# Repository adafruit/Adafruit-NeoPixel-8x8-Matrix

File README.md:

# Adafruit-NeoPixel-8x8-Matrix 

__Format is EagleCAD schematic and board layout__

<a href="http://www.adafruit.com/products/1487"><br/>Click here to purchase one from the Adafruit shop</a>

Put on your sunglasses before wiring up this LED matrix - 64 eye-blistering RGB LEDs adorn the NeoMatrix for a blast of configurable color. Arranged in an 8x8 matrix, each pixel is individually addressable. Only one microcontroller pin is required to control all the LEDs, and you get 24 bit color for each LED.

Wiring it up is easy: there are two 3-pin connection ports. Solder wires to the input port and provide 5VDC to the +5V and ground pins, then connect the DIN pin to your microcontroller. If you're using our NeoPixel Arduino library, use digital #6. You'll also need to make a common ground from the 5V power supply to the microcontroller/Arduino. Since each LED can draw as much as 60mA (thats up to 3.5 Amps per panel if all LEDs are on bright white!) we suggest our 5V 2A power supply. For most uses, you'll see about 1-2A of current per panel.

If, say, you need MORE blinky, you can chain these together. For the second shield, connect the DIN connection to the first panel's DOUT. Also connect a ground pin together and power with 5V. There you go! You can chain as many as you'd like although after 4 or more panels you may run low on RAM if you're using an UNO. Watch your power usage too, you may need a 5V 10A power supply for so many of these!

There is a single data line with a very timing-specific protocol. Since the protocol is very sensitive to timing, it requires a real-time microconroller such as an AVR, Arduino, PIC, mbed, etc. It cannot be used with a Linux-based microcomputer or interpreted microcontroller such as the netduino or Basic Stamp. Our wonderfully-written Neopixel library for Arduino supports these pixels! As it requires hand-tuned assembly it is only for AVR cores but others may have ported this chip driver code so please google around. An 8MHz or faster processor is required.

[Our detailed NeoPixel Uberguide has everything you need to use NeoPixels in any shape and size. Including ready-to-go library & example code for the Arduino UNO/Duemilanove/Diecimila, Flora/Micro/Leonardo, Trinket/Gemma, Arduino Due & Arduino Mega/ADK (all versions)](http://learn.adafruit.com/adafruit-neopixel-uberguide)

## License

Adafruit invests time and resources providing this open source design, 
please support Adafruit and open-source hardware by purchasing 
products from Adafruit!

Designed by Adafruit Industries.  
Creative Commons Attribution, Share-Alike license, check license.txt for more information
All text above must be included in any redistribution

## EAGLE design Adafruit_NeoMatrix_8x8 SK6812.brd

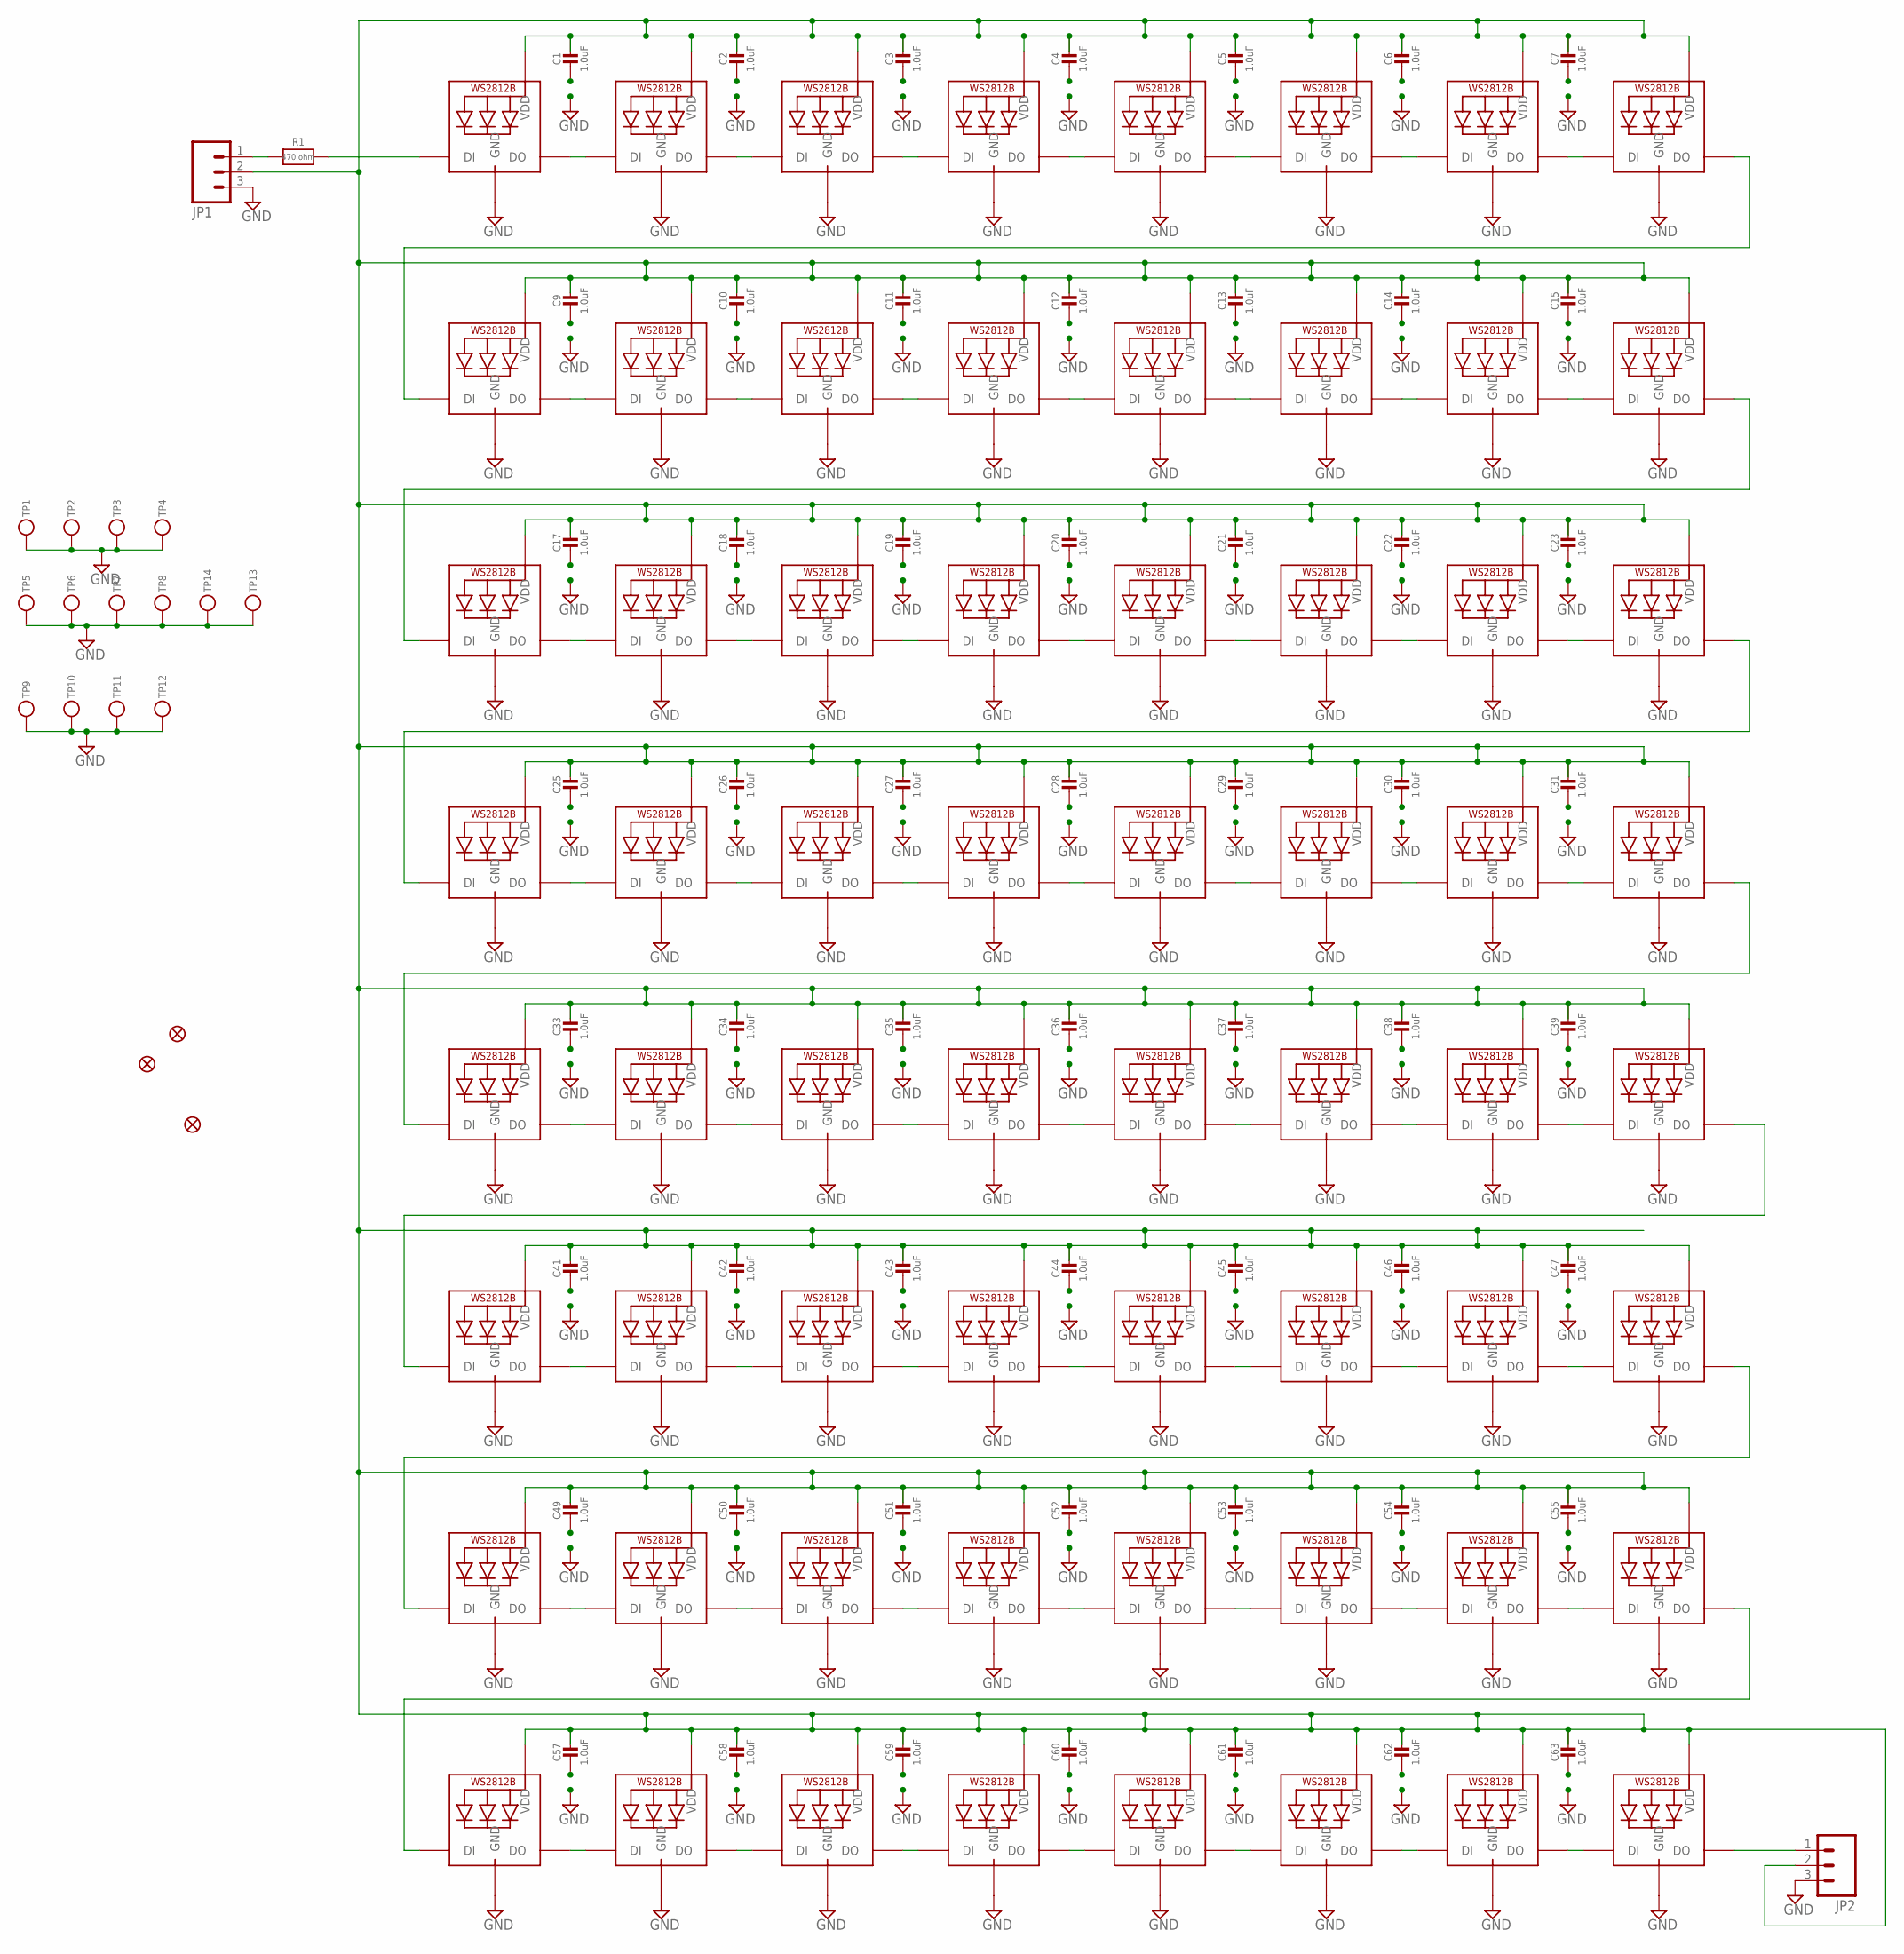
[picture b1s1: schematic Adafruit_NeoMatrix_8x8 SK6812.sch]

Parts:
C1, C2, C3, C4, C5, C6, C7, C9, C10, C11, C12, C13, C14, C15, C17, C18, C19, C20, C21, C22, C23, C25, C26, C27, C28, C29, C30, C31, C33, C34, C35, C36, C37, C38, C39, C41, C42, C43, C44, C45, C46, C47, C49, C50, C51, C52, C53, C54, C55, C57, C58, C59, C60, C61, C62, C63: 1.0uF; 0805-NO
FID1, FID2, FID3: FIDUCIAL_1MM
JP1, JP2: M03PTH; 1X03
LED1, LED2, LED3, LED4, LED5, LED6, LED7, LED8, LED9, LED10, LED11, LED12, LED13, LED14, LED15, LED16, LED17, LED18, LED19, LED20, LED21, LED22, LED23, LED24, LED25, LED26, LED27, LED28, LED29, LED30, LED31, LED32, LED33, LED34, LED35, LED36, LED37, LED38, LED39, LED40, LED41, LED42, LED43, LED44, LED45, LED46, LED47, LED48, LED49, LED50, LED51, LED52, LED53, LED54, LED55, LED56, LED57, LED58, LED59, LED60, LED61, LED62, LED63, LED64: WS2812B5050; WS2812B
R1: 470 ohm; 0805-NO
TP1, TP2, TP3, TP4, TP5, TP6, TP7, TP8, TP9, TP10, TP11, TP12, TP13, TP14: TESTPOINT; TESTPOINT_SMT

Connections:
GND: C1.2, C2.2, C3.2, C4.2, C5.2, C6.2, C7.2, C9.2, C10.2, C11.2, C12.2, C13.2, C14.2, C15.2, C17.2, C18.2, C19.2, C20.2, C21.2, C22.2, C23.2, C25.2, C26.2, C27.2, C28.2, C29.2, C30.2, C31.2, C33.2, C34.2, C35.2, C36.2, C37.2, C38.2, C39.2, C41.2, C42.2, C43.2, C44.2, C45.2, C46.2, C47.2, C49.2, C50.2, C51.2, C52.2, C53.2, C54.2, C55.2, C57.2, C58.2, C59.2, C60.2, C61.2, C62.2, C63.2, JP1.3, JP2.3, LED1.3-GND (GND), LED2.3-GND (GND), LED3.3-GND (GND), LED4.3-GND (GND), LED5.3-GND (GND), LED6.3-GND (GND), LED7.3-GND (GND), LED8.3-GND (GND), LED9.3-GND (GND), LED10.3-GND (GND), LED11.3-GND (GND), LED12.3-GND (GND), LED13.3-GND (GND), LED14.3-GND (GND), LED15.3-GND (GND), LED16.3-GND (GND), LED17.3-GND (GND), LED18.3-GND (GND), LED19.3-GND (GND), LED20.3-GND (GND), LED21.3-GND (GND), LED22.3-GND (GND), LED23.3-GND (GND), LED24.3-GND (GND), LED25.3-GND (GND), LED26.3-GND (GND), LED27.3-GND (GND), LED28.3-GND (GND), LED29.3-GND (GND), LED30.3-GND (GND), LED31.3-GND (GND), LED32.3-GND (GND), LED33.3-GND (GND), LED34.3-GND (GND), LED35.3-GND (GND), LED36.3-GND (GND), LED37.3-GND (GND), LED38.3-GND (GND), LED39.3-GND (GND), LED40.3-GND (GND), LED41.3-GND (GND), LED42.3-GND (GND), LED43.3-GND (GND), LED44.3-GND (GND), LED45.3-GND (GND), LED46.3-GND (GND), LED47.3-GND (GND), LED48.3-GND (GND), LED49.3-GND (GND), LED50.3-GND (GND), LED51.3-GND (GND), LED52.3-GND (GND), LED53.3-GND (GND), LED54.3-GND (GND), LED55.3-GND (GND), LED56.3-GND (GND), LED57.3-GND (GND), LED58.3-GND (GND), LED59.3-GND (GND), LED60.3-GND (GND), LED61.3-GND (GND), LED62.3-GND (GND), LED63.3-GND (GND), LED64.3-GND (GND), TP1.P$1, TP2.P$1, TP3.P$1, TP4.P$1, TP5.P$1, TP6.P$1, TP7.P$1, TP8.P$1, TP9.P$1, TP10.P$1, TP11.P$1, TP12.P$1, TP13.P$1, TP14.P$1
unnamed: LED1.4-DIN (DI), R1.2
unnamed: LED8.2-DOUT (DO), LED9.4-DIN (DI)
unnamed: LED16.2-DOUT (DO), LED17.4-DIN (DI)
unnamed: LED24.2-DOUT (DO), LED25.4-DIN (DI)
unnamed: LED40.2-DOUT (DO), LED41.4-DIN (DI)
unnamed: LED32.2-DOUT (DO), LED33.4-DIN (DI)
unnamed: LED48.2-DOUT (DO), LED49.4-DIN (DI)
unnamed: LED56.2-DOUT (DO), LED57.4-DIN (DI)
unnamed: JP2.1, LED64.2-DOUT (DO)
unnamed: JP1.1, R1.1
unnamed: LED17.2-DOUT (DO), LED18.4-DIN (DI)
unnamed: LED25.2-DOUT (DO), LED26.4-DIN (DI)
unnamed: LED26.2-DOUT (DO), LED27.4-DIN (DI)
unnamed: LED2.2-DOUT (DO), LED3.4-DIN (DI)
unnamed: LED3.2-DOUT (DO), LED4.4-DIN (DI)
unnamed: LED4.2-DOUT (DO), LED5.4-DIN (DI)
unnamed: LED5.2-DOUT (DO), LED6.4-DIN (DI)
unnamed: LED6.2-DOUT (DO), LED7.4-DIN (DI)
unnamed: LED7.2-DOUT (DO), LED8.4-DIN (DI)
unnamed: LED10.2-DOUT (DO), LED11.4-DIN (DI)
unnamed: LED11.2-DOUT (DO), LED12.4-DIN (DI)
unnamed: LED12.2-DOUT (DO), LED13.4-DIN (DI)
unnamed: LED13.2-DOUT (DO), LED14.4-DIN (DI)
unnamed: LED14.2-DOUT (DO), LED15.4-DIN (DI)
unnamed: LED15.2-DOUT (DO), LED16.4-DIN (DI)
unnamed: LED18.2-DOUT (DO), LED19.4-DIN (DI)
unnamed: LED19.2-DOUT (DO), LED20.4-DIN (DI)
unnamed: LED20.2-DOUT (DO), LED21.4-DIN (DI)
unnamed: LED21.2-DOUT (DO), LED22.4-DIN (DI)
unnamed: LED22.2-DOUT (DO), LED23.4-DIN (DI)
unnamed: LED23.2-DOUT (DO), LED24.4-DIN (DI)
unnamed: LED27.2-DOUT (DO), LED28.4-DIN (DI)
unnamed: LED28.2-DOUT (DO), LED29.4-DIN (DI)
unnamed: LED29.2-DOUT (DO), LED30.4-DIN (DI)
unnamed: LED30.2-DOUT (DO), LED31.4-DIN (DI)
unnamed: LED31.2-DOUT (DO), LED32.4-DIN (DI)
unnamed: LED1.2-DOUT (DO), LED2.4-DIN (DI)
unnamed: LED9.2-DOUT (DO), LED10.4-DIN (DI)
unnamed: LED49.2-DOUT (DO), LED50.4-DIN (DI)
unnamed: LED57.2-DOUT (DO), LED58.4-DIN (DI)
unnamed: LED58.2-DOUT (DO), LED59.4-DIN (DI)
unnamed: LED34.2-DOUT (DO), LED35.4-DIN (DI)
unnamed: LED35.2-DOUT (DO), LED36.4-DIN (DI)
unnamed: LED36.2-DOUT (DO), LED37.4-DIN (DI)
unnamed: LED37.2-DOUT (DO), LED38.4-DIN (DI)
unnamed: LED38.2-DOUT (DO), LED39.4-DIN (DI)
unnamed: LED39.2-DOUT (DO), LED40.4-DIN (DI)
unnamed: LED42.2-DOUT (DO), LED43.4-DIN (DI)
unnamed: LED43.2-DOUT (DO), LED44.4-DIN (DI)
unnamed: LED44.2-DOUT (DO), LED45.4-DIN (DI)
unnamed: LED45.2-DOUT (DO), LED46.4-DIN (DI)
unnamed: LED46.2-DOUT (DO), LED47.4-DIN (DI)
unnamed: LED47.2-DOUT (DO), LED48.4-DIN (DI)
unnamed: LED50.2-DOUT (DO), LED51.4-DIN (DI)
unnamed: LED51.2-DOUT (DO), LED52.4-DIN (DI)
unnamed: LED52.2-DOUT (DO), LED53.4-DIN (DI)
unnamed: LED53.2-DOUT (DO), LED54.4-DIN (DI)
unnamed: LED54.2-DOUT (DO), LED55.4-DIN (DI)
unnamed: LED55.2-DOUT (DO), LED56.4-DIN (DI)
unnamed: LED59.2-DOUT (DO), LED60.4-DIN (DI)
unnamed: LED60.2-DOUT (DO), LED61.4-DIN (DI)
unnamed: LED61.2-DOUT (DO), LED62.4-DIN (DI)
unnamed: LED62.2-DOUT (DO), LED63.4-DIN (DI)
unnamed: LED63.2-DOUT (DO), LED64.4-DIN (DI)
unnamed: LED33.2-DOUT (DO), LED34.4-DIN (DI)
unnamed: LED41.2-DOUT (DO), LED42.4-DIN (DI)
VDD: C1.1, C2.1, C3.1, C4.1, C5.1, C6.1, C7.1, C9.1, C10.1, C11.1, C12.1, C13.1, C14.1, C15.1, C17.1, C18.1, C19.1, C20.1, C21.1, C22.1, C23.1, C25.1, C26.1, C27.1, C28.1, C29.1, C30.1, C31.1, C33.1, C34.1, C35.1, C36.1, C37.1, C38.1, C39.1, C41.1, C42.1, C43.1, C44.1, C45.1, C46.1, C47.1, C49.1, C50.1, C51.1, C52.1, C53.1, C54.1, C55.1, C57.1, C58.1, C59.1, C60.1, C61.1, C62.1, C63.1, JP1.2, JP2.2, LED1.1-VDD (VDD), LED2.1-VDD (VDD), LED3.1-VDD (VDD), LED4.1-VDD (VDD), LED5.1-VDD (VDD), LED6.1-VDD (VDD), LED7.1-VDD (VDD), LED8.1-VDD (VDD), LED9.1-VDD (VDD), LED10.1-VDD (VDD), LED11.1-VDD (VDD), LED12.1-VDD (VDD), LED13.1-VDD (VDD), LED14.1-VDD (VDD), LED15.1-VDD (VDD), LED16.1-VDD (VDD), LED17.1-VDD (VDD), LED18.1-VDD (VDD), LED19.1-VDD (VDD), LED20.1-VDD (VDD), LED21.1-VDD (VDD), LED22.1-VDD (VDD), LED23.1-VDD (VDD), LED24.1-VDD (VDD), LED25.1-VDD (VDD), LED26.1-VDD (VDD), LED27.1-VDD (VDD), LED28.1-VDD (VDD), LED29.1-VDD (VDD), LED30.1-VDD (VDD), LED31.1-VDD (VDD), LED32.1-VDD (VDD), LED33.1-VDD (VDD), LED34.1-VDD (VDD), LED35.1-VDD (VDD), LED36.1-VDD (VDD), LED37.1-VDD (VDD), LED38.1-VDD (VDD), LED39.1-VDD (VDD), LED40.1-VDD (VDD), LED41.1-VDD (VDD), LED42.1-VDD (VDD), LED43.1-VDD (VDD), LED44.1-VDD (VDD), LED45.1-VDD (VDD), LED46.1-VDD (VDD), LED47.1-VDD (VDD), LED48.1-VDD (VDD), LED49.1-VDD (VDD), LED50.1-VDD (VDD), LED51.1-VDD (VDD), LED52.1-VDD (VDD), LED53.1-VDD (VDD), LED54.1-VDD (VDD), LED55.1-VDD (VDD), LED56.1-VDD (VDD), LED57.1-VDD (VDD), LED58.1-VDD (VDD), LED59.1-VDD (VDD), LED60.1-VDD (VDD), LED61.1-VDD (VDD), LED62.1-VDD (VDD), LED63.1-VDD (VDD), LED64.1-VDD (VDD)

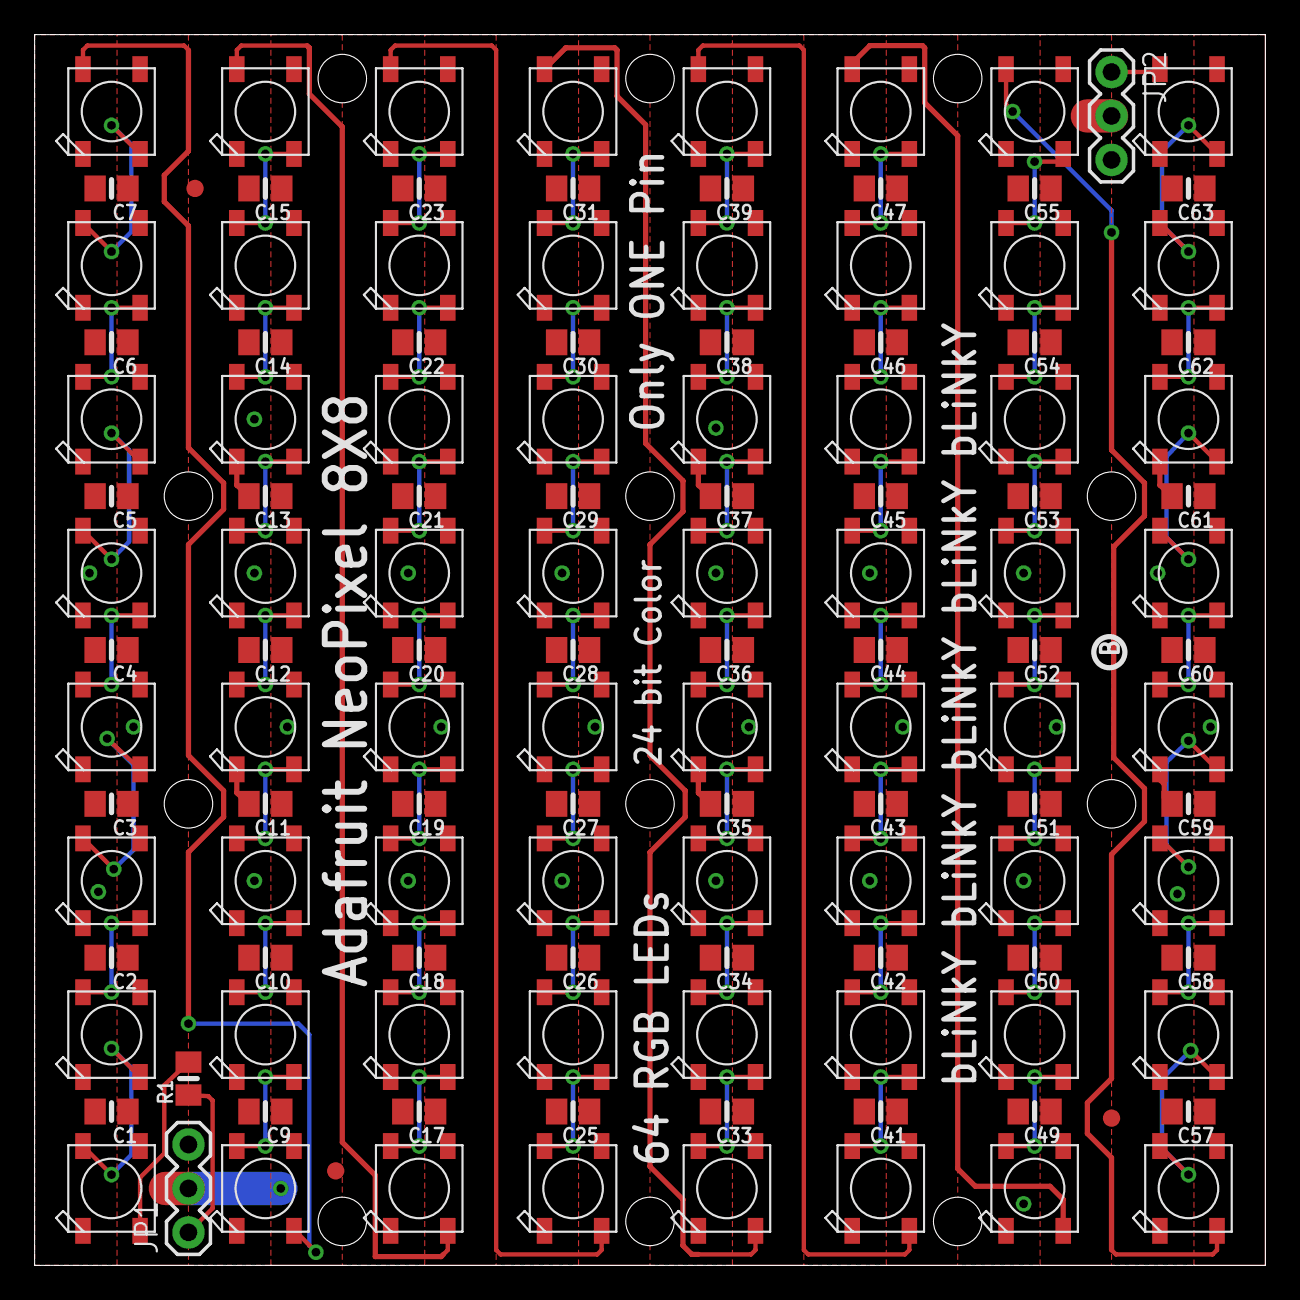
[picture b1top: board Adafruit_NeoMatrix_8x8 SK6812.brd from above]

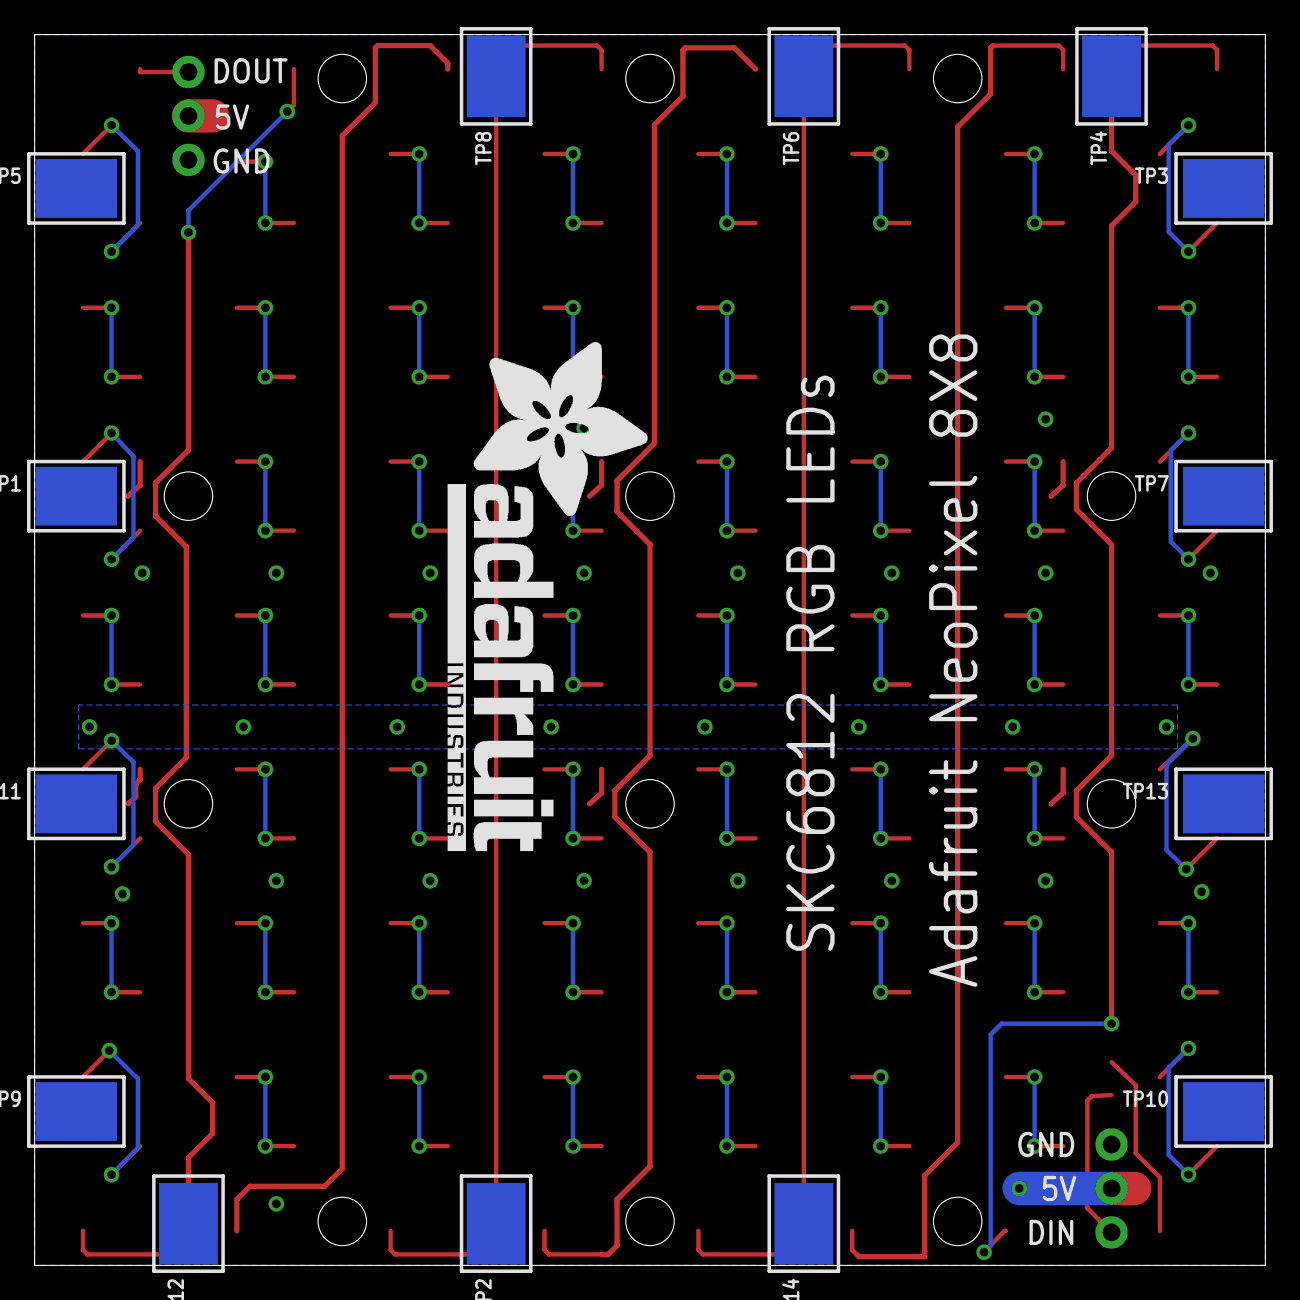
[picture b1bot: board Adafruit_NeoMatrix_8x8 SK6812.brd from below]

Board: 2 copper layers, 71.1 x 71.1 mm, 142 parts (15 on the bottom side), 68 nets.

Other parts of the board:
U$1: ADAFRUIT_TEXT_30MM
U$2: PCBFEAT-REV-040

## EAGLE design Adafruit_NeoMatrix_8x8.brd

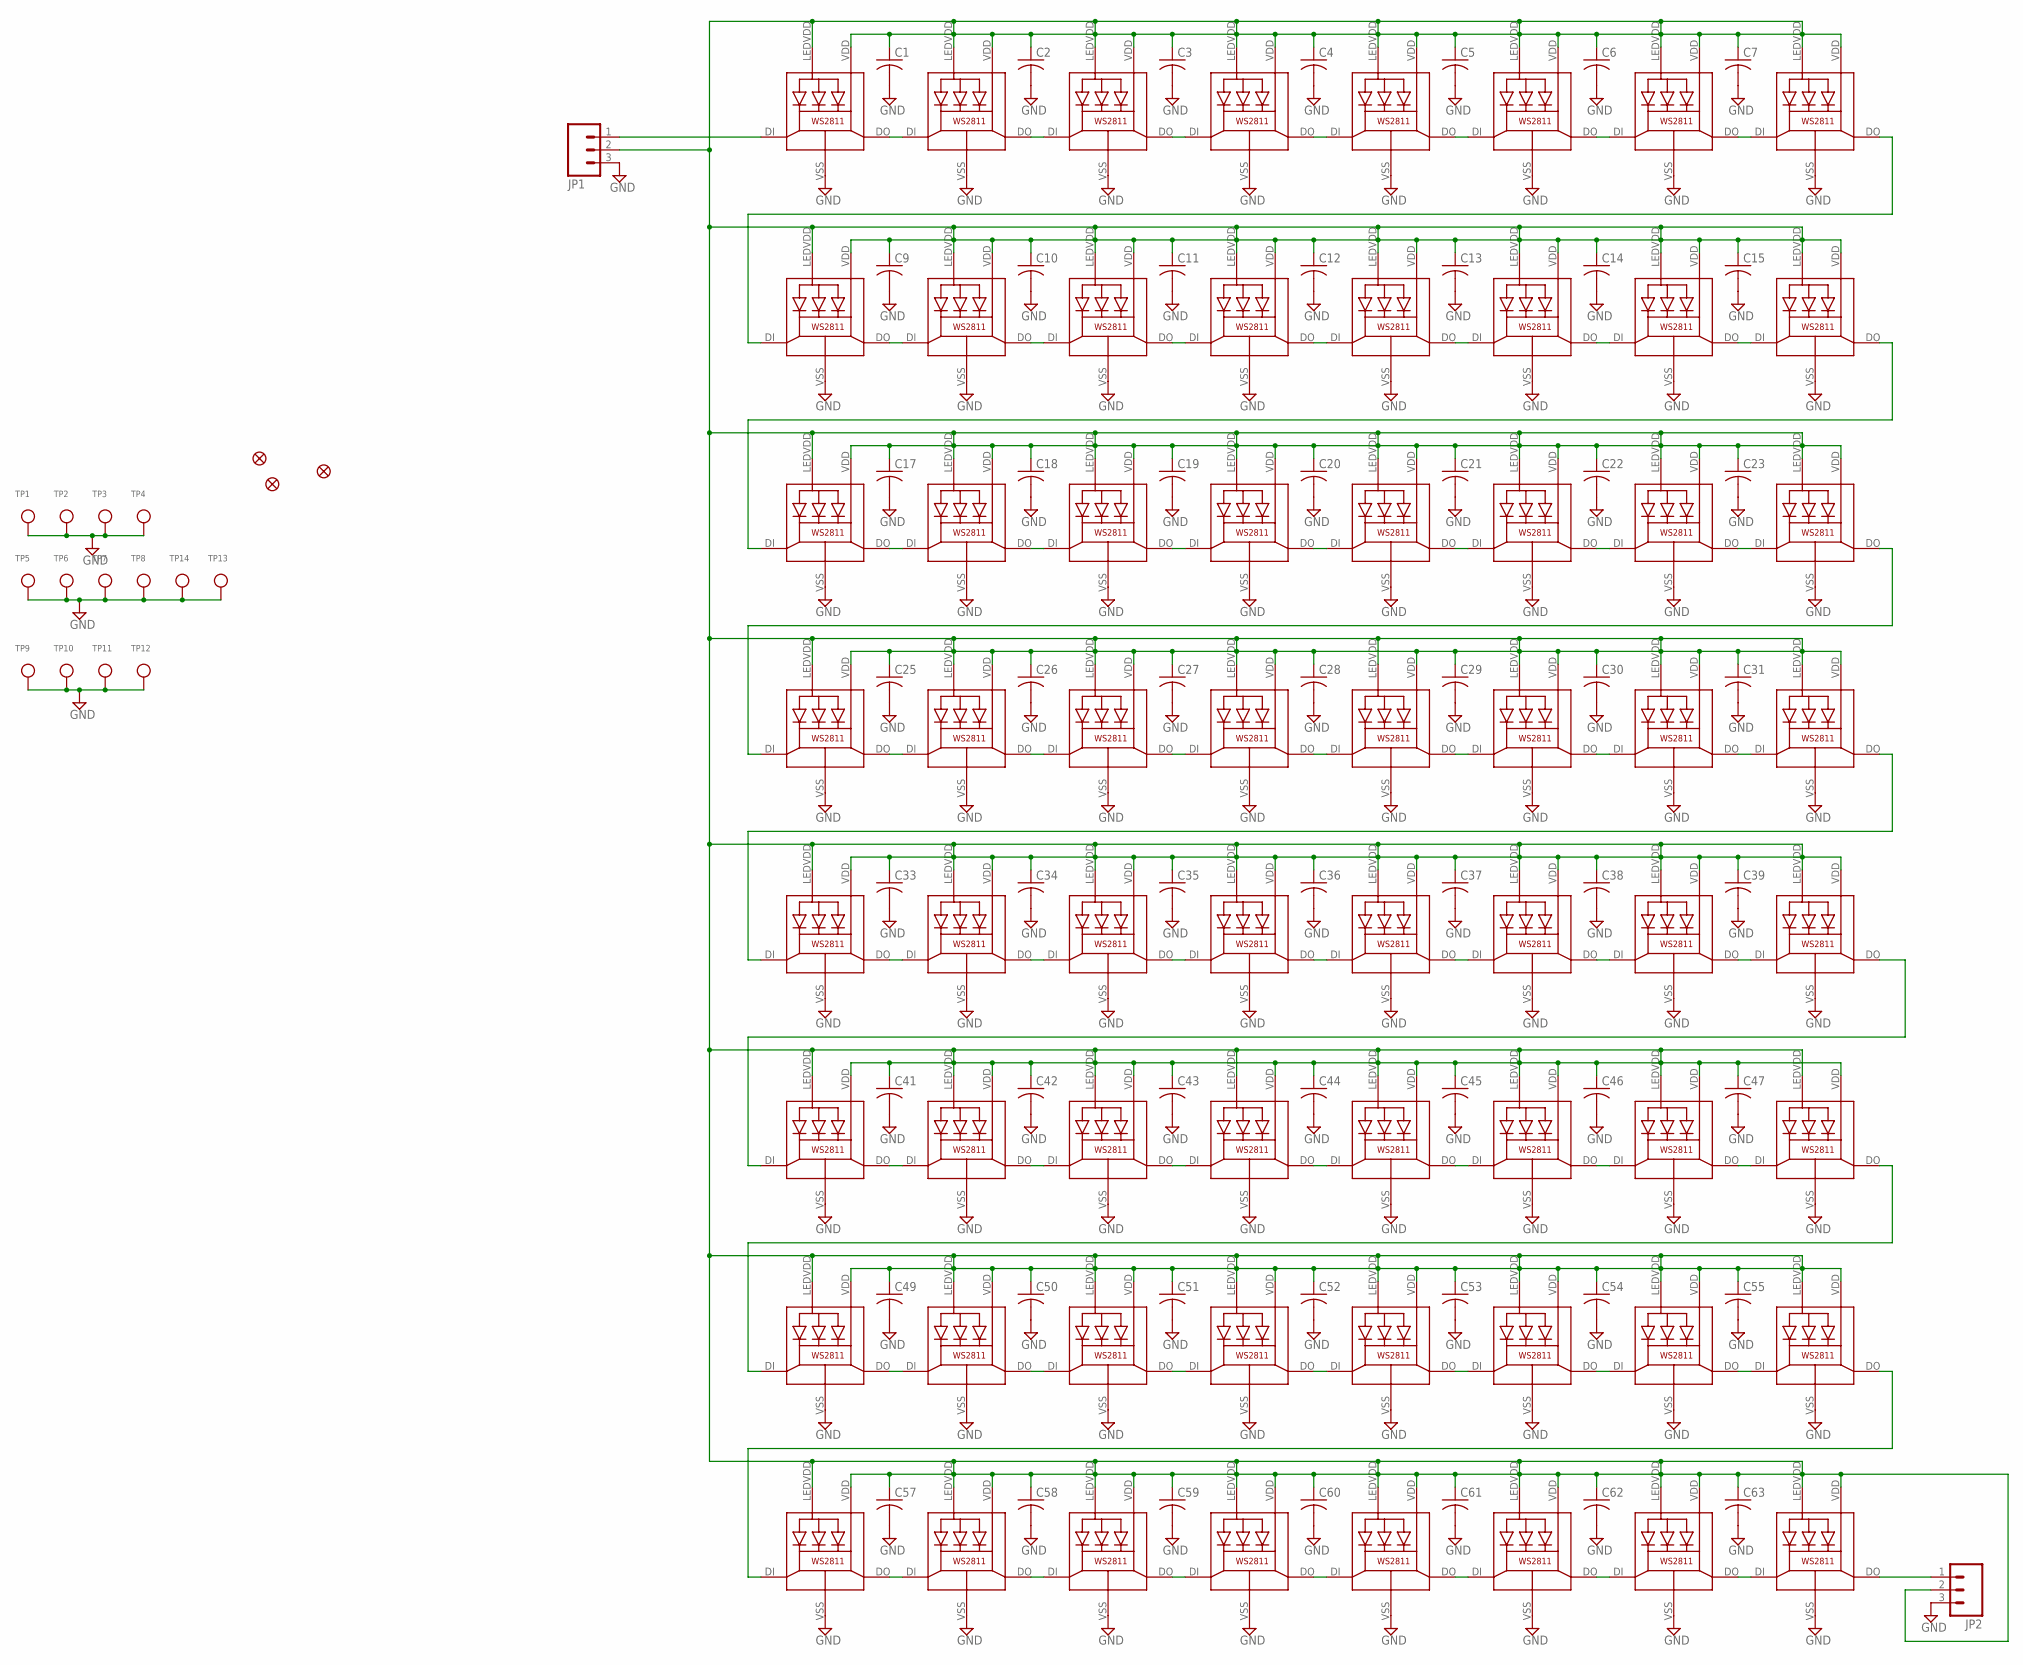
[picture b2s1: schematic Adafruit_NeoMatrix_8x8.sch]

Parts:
C1, C2, C3, C4, C5, C6, C7, C9, C10, C11, C12, C13, C14, C15, C17, C18, C19, C20, C21, C22, C23, C25, C26, C27, C28, C29, C30, C31, C33, C34, C35, C36, C37, C38, C39, C41, C42, C43, C44, C45, C46, C47, C49, C50, C51, C52, C53, C54, C55, C57, C58, C59, C60, C61, C62, C63: RCL_C-USC0805K; RCL_C0805K
FID1, FID2, FID3: FIDUCIAL""; FIDUCIAL_1MM
JP1, JP2: M03PTH; 1X03
LED1, LED2, LED3, LED4, LED5, LED6, LED7, LED8, LED9, LED10, LED11, LED12, LED13, LED14, LED15, LED16, LED17, LED18, LED19, LED20, LED21, LED22, LED23, LED24, LED25, LED26, LED27, LED28, LED29, LED30, LED31, LED32, LED33, LED34, LED35, LED36, LED37, LED38, LED39, LED40, LED41, LED42, LED43, LED44, LED45, LED46, LED47, LED48, LED49, LED50, LED51, LED52, LED53, LED54, LED55, LED56, LED57, LED58, LED59, LED60, LED61, LED62, LED63, LED64: WS28115050
TP1, TP2, TP3, TP4, TP5, TP6, TP7, TP8, TP9, TP10, TP11, TP12, TP13, TP14: TESTPOINT; TESTPOINT_SMT

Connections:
GND: C1.2, C2.2, C3.2, C4.2, C5.2, C6.2, C7.2, C9.2, C10.2, C11.2, C12.2, C13.2, C14.2, C15.2, C17.2, C18.2, C19.2, C20.2, C21.2, C22.2, C23.2, C25.2, C26.2, C27.2, C28.2, C29.2, C30.2, C31.2, C33.2, C34.2, C35.2, C36.2, C37.2, C38.2, C39.2, C41.2, C42.2, C43.2, C44.2, C45.2, C46.2, C47.2, C49.2, C50.2, C51.2, C52.2, C53.2, C54.2, C55.2, C57.2, C58.2, C59.2, C60.2, C61.2, C62.2, C63.2, JP1.3, JP2.3, LED1.VSS (GND), LED2.VSS (GND), LED3.VSS (GND), LED4.VSS (GND), LED5.VSS (GND), LED6.VSS (GND), LED7.VSS (GND), LED8.VSS (GND), LED9.VSS (GND), LED10.VSS (GND), LED11.VSS (GND), LED12.VSS (GND), LED13.VSS (GND), LED14.VSS (GND), LED15.VSS (GND), LED16.VSS (GND), LED17.VSS (GND), LED18.VSS (GND), LED19.VSS (GND), LED20.VSS (GND), LED21.VSS (GND), LED22.VSS (GND), LED23.VSS (GND), LED24.VSS (GND), LED25.VSS (GND), LED26.VSS (GND), LED27.VSS (GND), LED28.VSS (GND), LED29.VSS (GND), LED30.VSS (GND), LED31.VSS (GND), LED32.VSS (GND), LED33.VSS (GND), LED34.VSS (GND), LED35.VSS (GND), LED36.VSS (GND), LED37.VSS (GND), LED38.VSS (GND), LED39.VSS (GND), LED40.VSS (GND), LED41.VSS (GND), LED42.VSS (GND), LED43.VSS (GND), LED44.VSS (GND), LED45.VSS (GND), LED46.VSS (GND), LED47.VSS (GND), LED48.VSS (GND), LED49.VSS (GND), LED50.VSS (GND), LED51.VSS (GND), LED52.VSS (GND), LED53.VSS (GND), LED54.VSS (GND), LED55.VSS (GND), LED56.VSS (GND), LED57.VSS (GND), LED58.VSS (GND), LED59.VSS (GND), LED60.VSS (GND), LED61.VSS (GND), LED62.VSS (GND), LED63.VSS (GND), LED64.VSS (GND), TP1.P$1, TP2.P$1, TP3.P$1, TP4.P$1, TP5.P$1, TP6.P$1, TP7.P$1, TP8.P$1, TP9.P$1, TP10.P$1, TP11.P$1, TP12.P$1, TP13.P$1, TP14.P$1
unnamed: JP1.1, LED1.DI
unnamed: LED8.DO, LED9.DI
unnamed: LED16.DO, LED17.DI
unnamed: LED24.DO, LED25.DI
unnamed: LED40.DO, LED41.DI
unnamed: LED32.DO, LED33.DI
unnamed: LED48.DO, LED49.DI
unnamed: LED56.DO, LED57.DI
unnamed: JP2.1, LED64.DO
unnamed: LED17.DO, LED18.DI
unnamed: LED25.DO, LED26.DI
unnamed: LED26.DO, LED27.DI
unnamed: LED2.DO, LED3.DI
unnamed: LED3.DO, LED4.DI
unnamed: LED4.DO, LED5.DI
unnamed: LED5.DO, LED6.DI
unnamed: LED6.DO, LED7.DI
unnamed: LED7.DO, LED8.DI
unnamed: LED10.DO, LED11.DI
unnamed: LED11.DO, LED12.DI
unnamed: LED12.DO, LED13.DI
unnamed: LED13.DO, LED14.DI
unnamed: LED14.DO, LED15.DI
unnamed: LED15.DO, LED16.DI
unnamed: LED18.DO, LED19.DI
unnamed: LED19.DO, LED20.DI
unnamed: LED20.DO, LED21.DI
unnamed: LED21.DO, LED22.DI
unnamed: LED22.DO, LED23.DI
unnamed: LED23.DO, LED24.DI
unnamed: LED27.DO, LED28.DI
unnamed: LED28.DO, LED29.DI
unnamed: LED29.DO, LED30.DI
unnamed: LED30.DO, LED31.DI
unnamed: LED31.DO, LED32.DI
unnamed: LED1.DO, LED2.DI
unnamed: LED9.DO, LED10.DI
unnamed: LED49.DO, LED50.DI
unnamed: LED57.DO, LED58.DI
unnamed: LED58.DO, LED59.DI
unnamed: LED34.DO, LED35.DI
unnamed: LED35.DO, LED36.DI
unnamed: LED36.DO, LED37.DI
unnamed: LED37.DO, LED38.DI
unnamed: LED38.DO, LED39.DI
unnamed: LED39.DO, LED40.DI
unnamed: LED42.DO, LED43.DI
unnamed: LED43.DO, LED44.DI
unnamed: LED44.DO, LED45.DI
unnamed: LED45.DO, LED46.DI
unnamed: LED46.DO, LED47.DI
unnamed: LED47.DO, LED48.DI
unnamed: LED50.DO, LED51.DI
unnamed: LED51.DO, LED52.DI
unnamed: LED52.DO, LED53.DI
unnamed: LED53.DO, LED54.DI
unnamed: LED54.DO, LED55.DI
unnamed: LED55.DO, LED56.DI
unnamed: LED59.DO, LED60.DI
unnamed: LED60.DO, LED61.DI
unnamed: LED61.DO, LED62.DI
unnamed: LED62.DO, LED63.DI
unnamed: LED63.DO, LED64.DI
unnamed: LED33.DO, LED34.DI
unnamed: LED41.DO, LED42.DI
VDD: C1.1, C2.1, C3.1, C4.1, C5.1, C6.1, C7.1, C9.1, C10.1, C11.1, C12.1, C13.1, C14.1, C15.1, C17.1, C18.1, C19.1, C20.1, C21.1, C22.1, C23.1, C25.1, C26.1, C27.1, C28.1, C29.1, C30.1, C31.1, C33.1, C34.1, C35.1, C36.1, C37.1, C38.1, C39.1, C41.1, C42.1, C43.1, C44.1, C45.1, C46.1, C47.1, C49.1, C50.1, C51.1, C52.1, C53.1, C54.1, C55.1, C57.1, C58.1, C59.1, C60.1, C61.1, C62.1, C63.1, JP1.2, JP2.2, LED1.LEDVDD, LED1.VDD, LED2.LEDVDD, LED2.VDD, LED3.LEDVDD, LED3.VDD, LED4.LEDVDD, LED4.VDD, LED5.LEDVDD, LED5.VDD, LED6.LEDVDD, LED6.VDD, LED7.LEDVDD, LED7.VDD, LED8.LEDVDD, LED8.VDD, LED9.LEDVDD, LED9.VDD, LED10.LEDVDD, LED10.VDD, LED11.LEDVDD, LED11.VDD, LED12.LEDVDD, LED12.VDD, LED13.LEDVDD, LED13.VDD, LED14.LEDVDD, LED14.VDD, LED15.LEDVDD, LED15.VDD, LED16.LEDVDD, LED16.VDD, LED17.LEDVDD, LED17.VDD, LED18.LEDVDD, LED18.VDD, LED19.LEDVDD, LED19.VDD, LED20.LEDVDD, LED20.VDD, LED21.LEDVDD, LED21.VDD, LED22.LEDVDD, LED22.VDD, LED23.LEDVDD, LED23.VDD, LED24.LEDVDD, LED24.VDD, LED25.LEDVDD, LED25.VDD, LED26.LEDVDD, LED26.VDD, LED27.LEDVDD, LED27.VDD, LED28.LEDVDD, LED28.VDD, LED29.LEDVDD, LED29.VDD, LED30.LEDVDD, LED30.VDD, LED31.LEDVDD, LED31.VDD, LED32.LEDVDD, LED32.VDD, LED33.LEDVDD, LED33.VDD, LED34.LEDVDD, LED34.VDD, LED35.LEDVDD, LED35.VDD, LED36.LEDVDD, LED36.VDD, LED37.LEDVDD, LED37.VDD, LED38.LEDVDD, LED38.VDD, LED39.LEDVDD, LED39.VDD, LED40.LEDVDD, LED40.VDD, LED41.LEDVDD, LED41.VDD, LED42.LEDVDD, LED42.VDD, LED43.LEDVDD, LED43.VDD, LED44.LEDVDD, LED44.VDD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

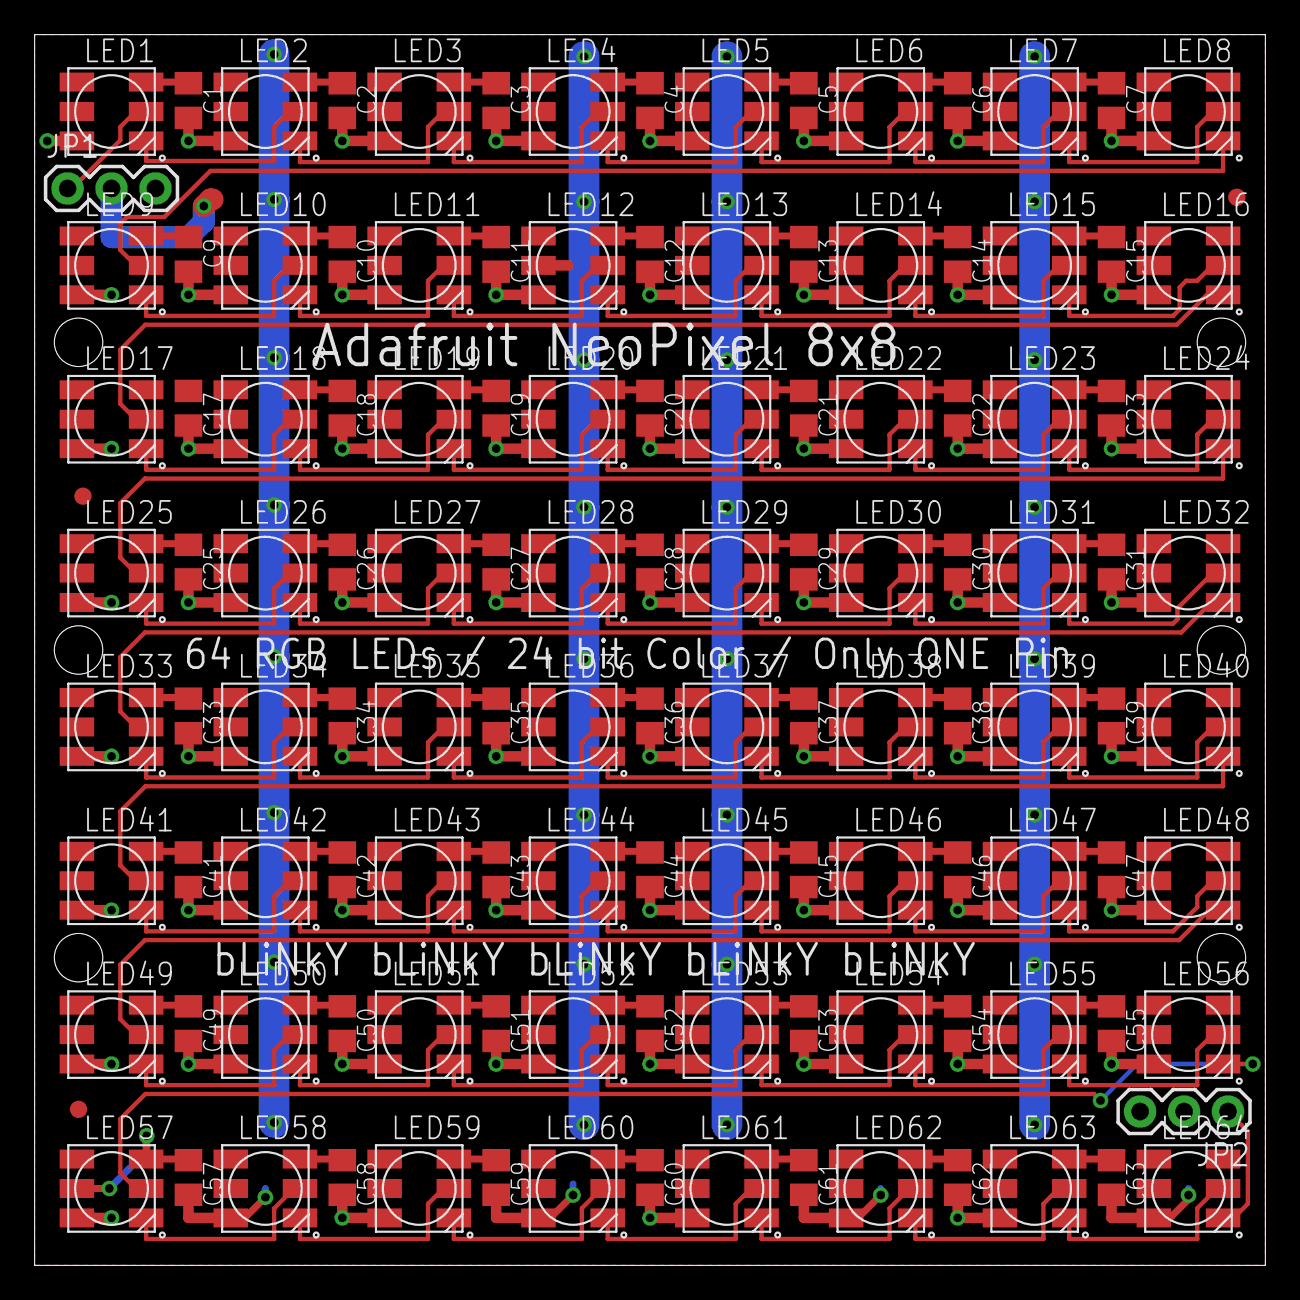
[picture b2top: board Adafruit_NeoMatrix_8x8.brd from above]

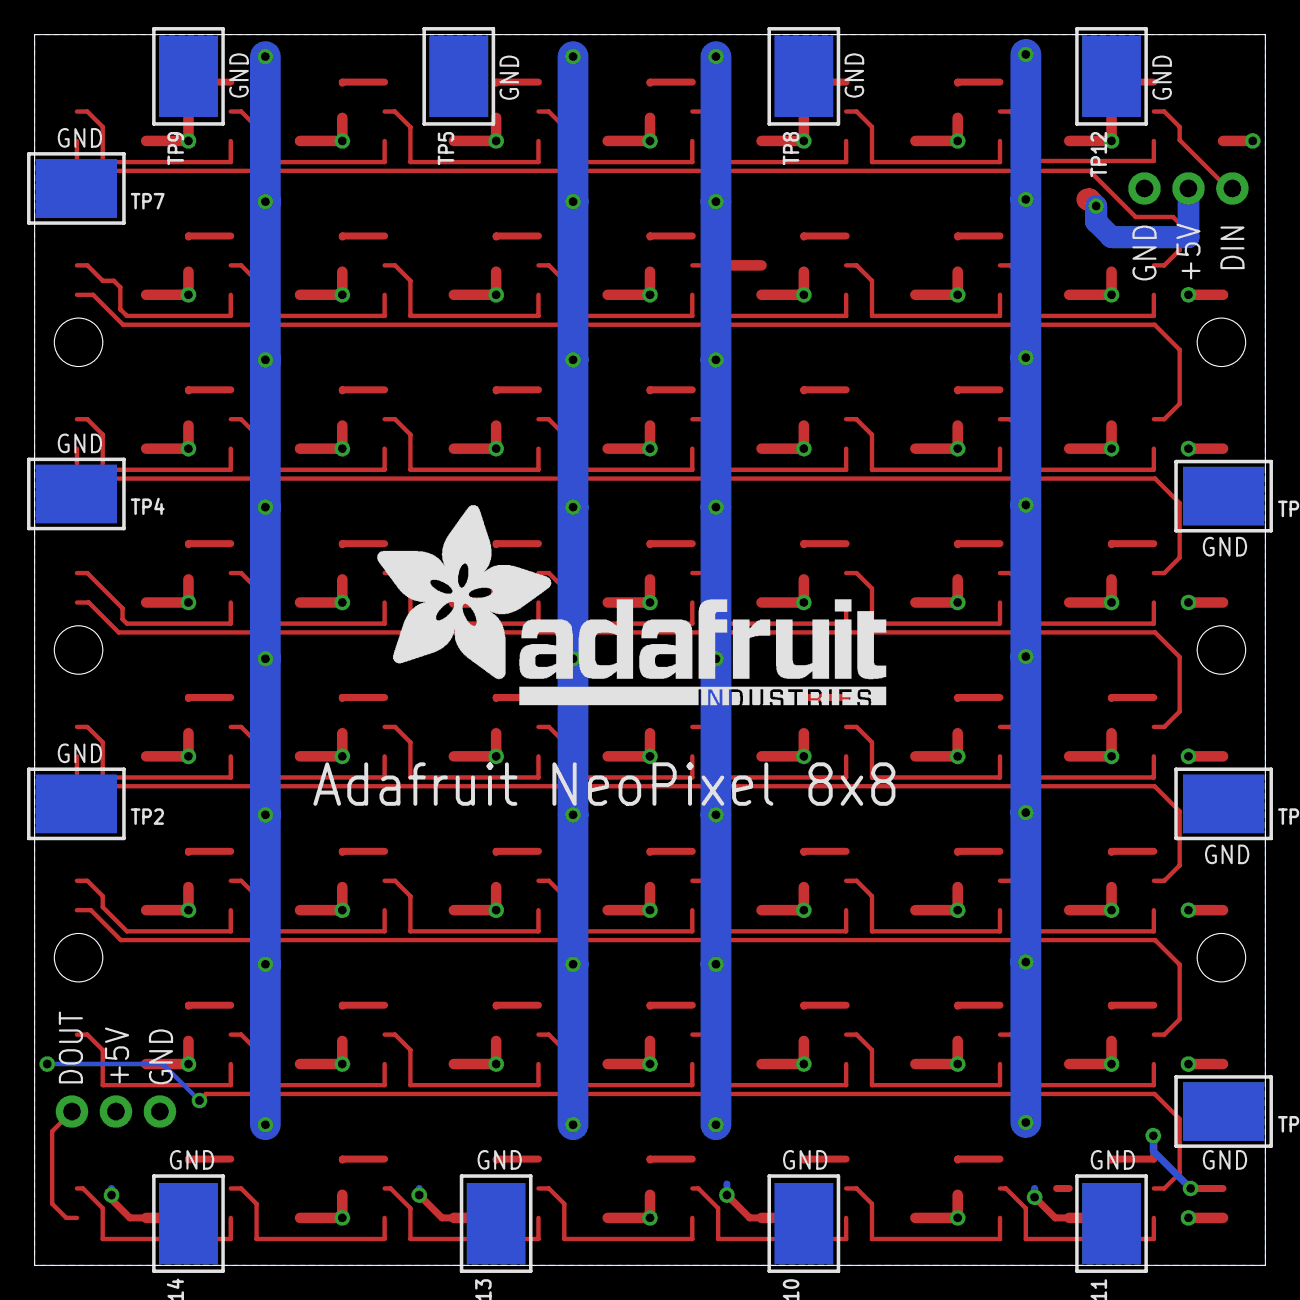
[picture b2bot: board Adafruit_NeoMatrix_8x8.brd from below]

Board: 2 copper layers, 71.1 x 71.1 mm, 140 parts (15 on the bottom side), 67 nets.

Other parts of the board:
U$1: ADAFRUIT_TEXT_30MM

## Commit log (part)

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2014-02-04 init
2014-02-04 read!
2015-09-09 now with 'B type neopixels
2019-06-14 readme + image
2019-06-14 add missing license

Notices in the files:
parts and their libraries:
microbuilder: This work is placed in the public domain, and may be freely used for commercial and non-commercial work with the following conditions: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
